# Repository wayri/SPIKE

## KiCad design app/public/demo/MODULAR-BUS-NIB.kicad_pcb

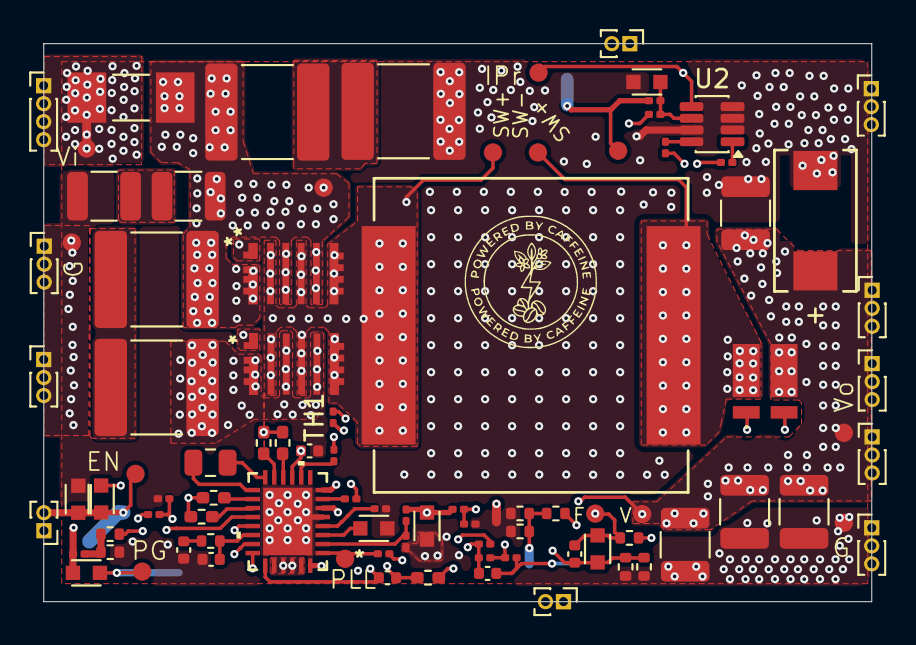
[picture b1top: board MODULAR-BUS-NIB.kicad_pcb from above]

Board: 6 copper layers, 46.0 x 31.0 mm, 91 parts (0 on the bottom side), 45 nets.

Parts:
C1, C2, C3, C4: 15u_100V_2220; C_2220_5750Metric
C9, C10: 4.7u_100V_1210; C_1210_3225Metric
C11: 33u_35V_2917; CAPMP7.6X4.3_3.1N_KEM-L
C13, C14, C15, C16: 22u_25V_1210; C_1210_3225Metric
C17: 100n_100V_0805; C_0805_2012Metric
C18: 4.7u_16V_0603; C_0603
C19, C24: 1n_50V_0402; C_0402_1005Metric
C20: 47p_50V_0402; C_0402_1005Metric
C21: 100n_16V_0201; C_0201_0603Metric
C22: 430p_50V_0402; C_0402_1005Metric
C23: 200p_50V_0402; C_0402_1005Metric
C25: 100n_25V_0603; C_0603
C26: 100n_10V_0201; C_0201_0603Metric
F1: 10A_125V; FUSC6125X279N
J1: Conn_01x04_Pin; PinHeader_1x04_P1.00mm_Vertical
J9, J12, J21: Conn_01x02_Pin; PinHeader_1x02_P1.00mm_Vertical
J14, J15, J16, J17, J18, J19, J20: Conn_01x03_Pin; PinHeader_1x03_P1.00mm_Vertical
JP1, JP2: Jumper_2_Open; R_0201_0603Metric
L2: 8.2u_18A; IND_SRP1770TA_BRN-M
NT1: NetTie_2; NetTie-2_SMD_Pad0.5mm
Q1, Q2: EPC2306; EPC2302ENGRT_ECC
R3, R4: 2R_0.33W_0402; R_0402_1005Metric_Pad0.72x0.64mm_HandSolder
R5, R6: 4R_0.33W_0402; R_0402_1005Metric_Pad0.72x0.64mm_HandSolder
R7, R30: 0R_0.1W_0603; C_0603
R8: 100R_0.063W_0402; R_0402_1005Metric_Pad0.72x0.64mm_HandSolder
R9, R13, R16, R17, R18, R21, R22, R26, R27, R28, R29, R32: 0R_0.05W_0201; C_0201_0603Metric
R10: 5R1_0.07W_0402; R_0402_1005Metric
R11: 140K_0.1W_0603; R_0603
R12, R20, R35, R36, R37: 20K_0.1W_0402; R_0402_1005Metric
R14: 124K_0.21W_0603; R_0603
R15, R24: 15K_0.1W_0402; R_0402_1005Metric
R19: 0R002_3W_1216; WSK12162L000FEA
R23: 110K_0.1W_0603; R_0603
R25: 4.7K_0.1W_0402; R_0402_1005Metric
R33: 20K_0.05W_0201; C_0201_0603Metric
R34: 24K_0.07W_0201; C_0201_0603Metric
R39: 100K_0.05W_0402; C_0402_1005Metric
TH1: 100K_0201; R_0201_0603Metric
TP2, TP3, TP4, TP5, TP6, TP7, TP8, TP9, TP10, TP11, TP12, TP13, TP14, TP15: TestPoint; TestPoint-1.0mm
U1: LTC7891RUFDM-PBF; 05-08-1682_ADI
U2: INA241A3QDDFRQ1; SOT-23-8

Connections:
/12Vout: C11.1, C13.1, C14.1, C15.1, C16.1, J14.1, J14.2, J14.3, J15.1, J15.2, J15.3, J20.1, J20.2, J20.3, R9.1, R10.2, R19.3, R21.1, R24.1, R36.1, TP3.1 (1_1), TP8.1 (1_1)
/BuckModuleIP22-60-OP12-P120W-DR/BGDN: R6.1, U1.13 (BGDN)
/BuckModuleIP22-60-OP12-P120W-DR/BGUP: R5.1, U1.12 (BGUP)
/BuckModuleIP22-60-OP12-P120W-DR/EN: J21.2, R7.1, R30.2, TP12.1 (1_1), U1.28 (RUN)
/BuckModuleIP22-60-OP12-P120W-DR/GHS: Q1.1, R3.2, R4.2
/BuckModuleIP22-60-OP12-P120W-DR/GLS: Q2.1, R5.2, R6.2
/BuckModuleIP22-60-OP12-P120W-DR/INTVCC: C18.1, C24.2, R13.1, R28.2, R32.1, U1.8 (DRVCC), U1.11 (INTVCC), U1.24 (DTCB), U1.25 (DTCA), U1.26 (DRVSET), U1.27 (DRVUV)
/BuckModuleIP22-60-OP12-P120W-DR/ISNS+: JP1.1 (A), R8.2, R19.1
/BuckModuleIP22-60-OP12-P120W-DR/ISNS-: C19.1, JP2.1 (A), R19.2, U1.23 (SENSE-)
/BuckModuleIP22-60-OP12-P120W-DR/ITH: C23.1, R15.1, U1.20 (ITH)
/BuckModuleIP22-60-OP12-P120W-DR/PLL: R18.1, TP2.1 (1_1), U1.1 (PLLIN/SPREAD)
/BuckModuleIP22-60-OP12-P120W-DR/SW_node: L2.2, Q1.3, Q1.5, Q1.7, Q2.3, Q2.5, Q2.7, TP4.1 (1_1)
/BuckModuleIP22-60-OP12-P120W-DR/TGDN: R4.1, U1.16 (TGDN)
/BuckModuleIP22-60-OP12-P120W-DR/TGUP: R3.1, U1.17 (TGUP)
/BuckModuleIP22-60-OP12-P120W-DR/VFB: C20.2, R11.2, R12.1, R20.1, U1.21 (VFB)
/BuckModuleIP22-60-OP12-P120W-DR/VPRG: R28.1, R29.1, U1.6 (VPRG)
/BuckModuleIP22-60-OP12-P120W-DR/Vext_3V3: J12.2, R22.2, R23.1, R26.2, R33.2, TP13.1 (1_1)
/BuckModuleIP22-60-OP12-P120W-DR/Vin: C1.1, C3.1, C9.1, F1.2, Q1.2, Q1.4, Q1.6, R7.2, R17.1, R18.2, TP6.1 (1_1)
/IPRPM: J12.1, TP14.1 (1_1), U2.5
/PG: J21.1, R23.2, TP11.1 (1_1), U1.18 (PGOOD)
/Tsns: C26.1, J9.1, R39.1
/Vin_f: F1.1, J1.1, J1.2, J1.3, J1.4, TP9.1 (1_1)
/Vsns: J9.2, R35.1, R36.2, R37.1
GND: C2.2, C4.2, C10.2, C11.2, C13.2, C14.2, C15.2, C16.2, C18.2, C21.1, C22.2, C23.2, C24.1, C25.2, J16.1, J16.2, J16.3, J17.1, J17.2, J17.3, J18.1, J18.2, J18.3, J19.1, J19.2, J19.3, NT1.1, Q2.2, Q2.4, Q2.6, R12.2, R14.2, R16.1, R20.2, R25.2, R27.1, R29.2, R30.1, R35.2, R37.2, TP10.1 (1_1), TP15.1 (1_1), U1.5 (TEST), U1.29 (GND), U2.2 (GND), U2.3 (REF2), U2.4 (GND), U2.7 (REF1)
unnamed: C1.2, C2.1
unnamed: C3.2, C4.1
unnamed: C9.2, C10.1
unnamed: C20.1, R10.1, R11.1, TP7.1 (1_1)
unnamed: C22.1, R15.2
unnamed: C26.2, NT1.2, R34.1, TH1.2
unnamed: JP1.2 (B), U2.8 (+)
unnamed: JP2.2 (B), U2.1 (-)
unnamed: L2.1, R19.4, TP5.1 (1_1)
unnamed: R24.2, R25.1, R26.1
unnamed: R33.1, R34.2, R39.2, TH1.1
unnamed: C17.1, U1.14 (BOOST)
unnamed: R9.2, U1.10 (EXTVCC)
unnamed: R14.1, U1.3 (FREQ)
unnamed: R16.2, R32.2, U1.19 (ILIM)
unnamed: R13.2, R27.2, U1.2 (MODE)
unnamed: C19.2, R8.1, U1.22 (SENSE+)
unnamed: C17.2, U1.15 (SW)
unnamed: C21.2, U1.4 (TRACK/SS)
unnamed: R17.2, U1.7 (VIN)
unnamed: C25.1, R21.2, R22.1, U2.6 (V+)

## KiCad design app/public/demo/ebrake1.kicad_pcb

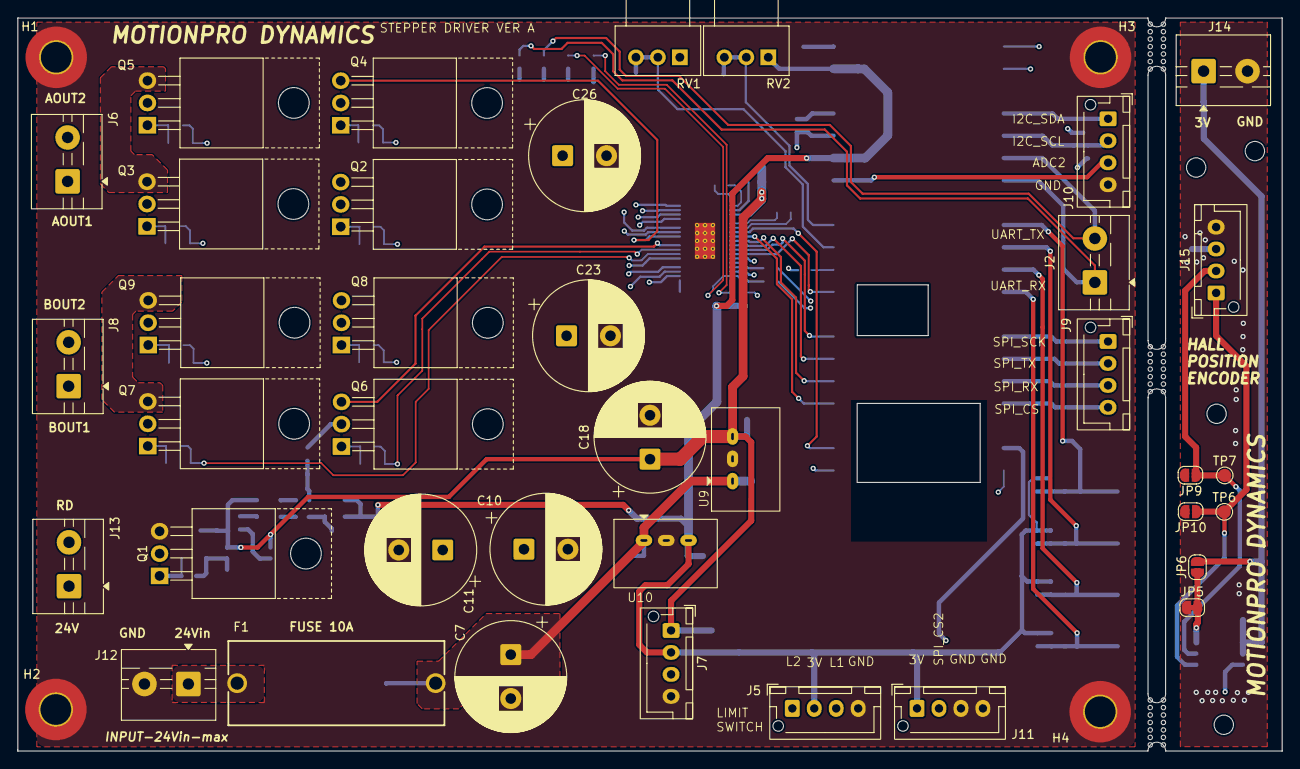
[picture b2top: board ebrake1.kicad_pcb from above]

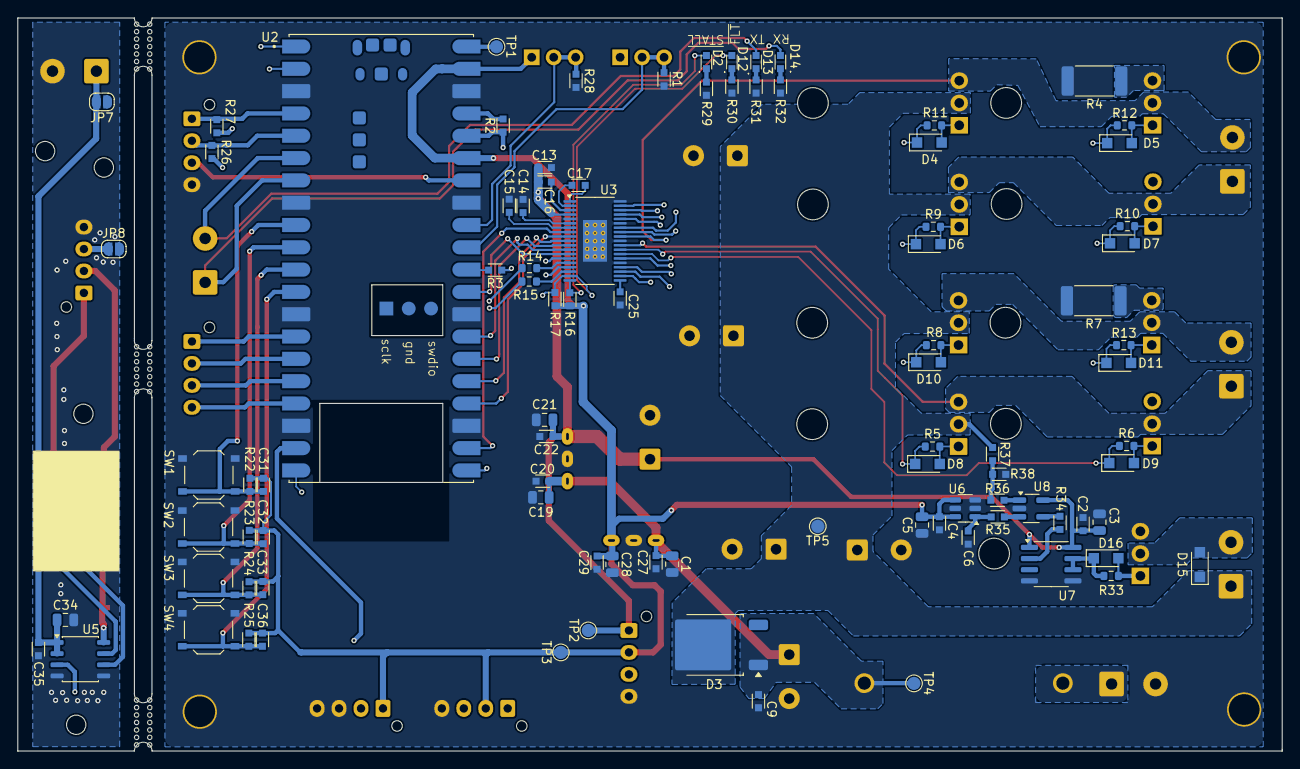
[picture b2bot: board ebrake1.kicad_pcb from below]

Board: 4 copper layers, 143.9 x 83.5 mm, 134 parts (92 on the bottom side), 84 nets.

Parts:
C1, C3, C5, C19, C21, C28, C34: 10u_50V; C_0805_2012Metric
C2, C4, C6, C9, C13, C15, C17, C20, C22, C27, C29, C31, C32, C33, C35, C36: 100n_50V; C_0603
C7, C10, C11, C18, C23, C26: 100u_100V; CP_Radial_D12.5mm_P5.00mm
C14, C16: 1u_50V; C_0603
C25: 1n_50V; C_0603
D2, D12: red; LED_0603
D3: 15A_100V; TO-252-2
D4, D5, D6, D7, D8, D9, D10, D11, D15, D16: SMD310HL-TP; Nexperia_CFP3_SOD-123W
D13, D14: yellow; LED_0603
F1: Fuse_holder_10A; 696108003002
H1, H2, H3, H4: MountingHole_Pad; MountingHole_3.5mm_Pad_TopOnly
J2, J6, J8, J12, J13, J14: stb01x02; TerminalBlock_MaiXu_MX126-5.0-02P_1x02_P5.00mm
J5, J7, J9, J10, J11, J15: 01x04; JST_XH_B4B-XH-AM_1x04_P2.50mm_Vertical
JP5: SolderJumper_2_Bridged; SolderJumper-2_P1.3mm_Bridged_RoundedPad1.0x1.5mm
JP6, JP7, JP8, JP9, JP10: SolderJumper_2_Open; SolderJumper-2_P1.3mm_Open_RoundedPad1.0x1.5mm
Q1, Q2, Q3, Q4, Q5, Q6, Q7, Q8, Q9: STP60NF06L; TO-220-3_Horizontal_TabUp
R1, R2, R3, R16, R17, R22, R23, R24, R25, R26, R27, R28, R29, R30, R31, R32, R34, R35, R36: 1k_0603; R_0603
R4, R7: 0.033R_2512; R_2512_6332Metric_Pad1.40x3.35mm_HandSolder
R5, R6, R8, R9, R10, R11, R12, R13, R14, R15, R33: 10R_0603; R_0603_1608Metric
R37: 10k_0603; R_0603
R38: 1.02k_0603; R_0603
RV1, RV2: R_Potentiometer_Trim; Potentiometer_Alps_RK09Y11_Single_Horizontal
SW1, SW2, SW3, SW4: SW_MEC_5E; SW_Push_1P1T_XKB_TS-1187A
TP1, TP2, TP3, TP4, TP5, TP6, TP7: TestPoint; TestPoint_Pad_D1.5mm
U2: SC0918; MODULE_SC0918
U3: DRV8711; HTSSOP-38-1EP_4.4x9.7mm_P0.5mm_EP2.74x4.75mm_ThermalVias
U5: AS5600L-ASOM; JEITA_SOIC-8_3.9x4.9mm_P1.27mm
U6: MCP1501-25xCH; SOT-23-6
U7: TC4420VOA713; SOIC-8_3.9x4.9mm_P1.27mm
U8: TLV1701AIDBVR; SOT-23-5_HandSoldering
U9: RBT10W24S12; rtb10_fp
U10: RBT10W24S3V3; rtb10_fp

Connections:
3Vin: C4.1, C5.1, C28.1, C29.1, C31.2, C32.2, C33.2, C36.2, J5.2, J7.2, J11.1, R16.2, R17.2, R22.1, R23.1, R24.1, R25.1, RV1.1, RV2.1, TP3.1, U2.35 (ADC_VREF), U2.39 (VSYS), U6.4 (~SHDN), U6.6 (VDD), U10.3 (Vout)
3Vout: R2.1, R3.1, R26.1, R27.1, U2.36 (3V3_OUT)
12V: C2.1, C3.1, C13.1, C16.1, C18.1, C21.1, C22.1, J7.1, TP2.1, U3.4 (VM), U7.1 (VDD), U7.8 (VDD), U8.5 (V+), U9.3 (Vout)
24V: C10.1, C11.1, C23.1, C26.1, D3.2 (K), D15.1 (K), J13.1, Q2.2 (D), Q4.2 (D), Q6.2 (D), Q8.2 (D), R37.2, TP5.1
24Vaux: C1.1, C7.1, C9.1, C19.1, C20.1, C27.1, D3.1 (A), F1.2, TP4.1, U9.1 (Vin), U10.1 (Vin)
/ADC0: R1.1, RV1.2, RV1.3, U2.31 (GP26)
/ADC1: R28.1, RV2.2, RV2.3, U2.32 (GP27)
/ADC2: J10.3, U2.34 (GP28)
/AOUT1: J6.1, Q2.3 (S), Q3.2 (D), U3.37 (AOUT1)
/AOUT2: J6.2, Q4.3 (S), Q5.2 (D), U3.30 (AOUT2)
/BIN1: U2.27 (GP21), U3.12 (BIN1)
/BIN2: U2.29 (GP22), U3.13 (BIN2)
/BOUT1: J8.1, Q6.3 (S), Q7.2 (D), U3.28 (BOUT1)
/BOUT2: J8.2, Q8.3 (S), Q9.2 (D), U3.21 (BOUT2)
/DIR: U2.26 (GP20), U3.11 (DIR/AIN2)
/ENC_OUT_ANLG: J15.3, JP8.1 (A), U5.3 (OUT)
/HBridge1/A1HS: D8.1 (K), R5.1, U3.27 (B1HS)
/HBridge1/A1LS: D9.1 (K), R6.1, U3.26 (B1LS)
/HBridge1/A2HS: D10.1 (K), R8.2, U3.22 (B2HS)
/HBridge1/A2LS: D11.1 (K), R13.2, U3.23 (B2LS)
/HBridge1/AISENP: Q7.3 (S), Q9.3 (S), R7.1, U3.25 (BISENP)
/HBridge/A1HS: D6.1 (K), R9.1, U3.36 (A1HS)
/HBridge/A1LS: D7.1 (K), R10.1, U3.35 (A1LS)
/HBridge/A2HS: D4.1 (K), R11.2, U3.31 (A2HS)
/HBridge/A2LS: D5.1 (K), R12.2, U3.32 (A2LS)
/HBridge/AISENP: Q3.3 (S), Q5.3 (S), R4.1, U3.34 (AISENP)
/I2C0_SCL: J10.2, R26.2, U2.5 (GP3)
/I2C0_SDA: J10.1, R27.2, U2.4 (GP2)
/LIM_SW1: J5.1, U2.1 (GP0)
/LIM_SW2: J5.3, U2.2 (GP1)
/RESET: U2.24 (GP18), U3.9 (RESET)
/SPI1_CS: J9.4, U2.17 (GP13), U3.16 (SCS)
/SPI1_CS2: J11.2, U2.19 (GP14)
/SPI1_RX: J9.3, R15.1, U2.16 (GP12)
/SPI1_SCK: J9.1, U2.14 (GP10), U3.14 (SCLK)
/SPI1_TX: J9.2, R14.1, U2.15 (GP11)
/STEP: U2.25 (GP19), U3.10 (STEP/AIN1)
/SW1: C31.1, R22.2, SW1.2, U2.9 (GP6)
/SW2: C32.1, R23.2, SW2.2, U2.10 (GP7)
/SW3: C33.1, R24.2, SW3.2, U2.11 (GP8)
/SW4: C36.1, R25.2, SW4.2, U2.12 (GP9)
/UART1_RX: D14.2 (A), J2.1, U2.7 (GP5)
/UART1_TX: D13.2 (A), J2.2, U2.6 (GP4)
/VCC_3V3: C34.1, C35.1, J14.1, JP6.2 (B), JP7.2 (B), U5.1 (VDD5V), U5.2 (VDD3V3)
/~FLT: D12.2 (A), R17.1, U2.20 (GP15), U3.18 (FAULTn)
/~SLEEP: U2.22 (GP17), U3.8 (SLEEPn)
/~STALL: D2.2 (A), R16.1, U2.21 (GP16), U3.19 (STALLn/BEMFVn)
GND: C1.2, C2.2, C3.2, C4.2, C5.2, C6.2, C7.2, C9.2, C10.2, C11.2, C13.2, C14.2, C15.2, C18.2, C19.2, C20.2, C21.2, C22.2, C23.2, C25.2, C26.2, C27.2, C28.2, C29.2, C34.2, C35.2, H1.1, H2.1, H3.1, H4.1, J5.4, J7.4, J10.4, J11.3, J11.4, J12.2, J14.2, J15.4, JP5.1 (A), Q1.3 (S), R1.2, R4.2, R7.2, R28.2, R29.2, R30.2, R31.2, R32.2, R38.1, SW1.1, SW2.1, SW3.1, SW4.1, U2.3 (GND), U2.8 (GND__1), U2.13 (GND__2), U2.18 (GND__3), U2.23 (GND__4), U2.28 (GND__5), U2.33 (AGND), U2.38 (GND__6), U2.F (GND__7), U3.5 (GND), U3.24 (BISENN), U3.29 (GND), U3.33 (AISENN), U3.38 (GND), U3.39 (GND), U5.4 (GND), U5.5 (PGO), U6.2 (GND), U6.3 (GND), U6.5 (GND), U7.4 (GND), U7.5 (GND), U8.2 (V-), U9.2 (GND), U10.2 (GND)
unnamed: D2.1 (K), R29.1
unnamed: D4.2 (A), Q4.1 (G), R11.1
unnamed: D5.2 (A), Q5.1 (G), R12.1
unnamed: D6.2 (A), Q2.1 (G), R9.2
unnamed: D7.2 (A), Q3.1 (G), R10.2
unnamed: D8.2 (A), Q6.1 (G), R5.2
unnamed: D9.2 (A), Q7.1 (G), R6.2
unnamed: D10.2 (A), Q8.1 (G), R8.1
unnamed: D11.2 (A), Q9.1 (G), R13.1
unnamed: D12.1 (K), R30.1
unnamed: D13.1 (K), R31.1
unnamed: D14.1 (K), R32.1
unnamed: D15.2 (A), J13.2, Q1.2 (D)
unnamed: D16.2 (A), Q1.1 (G), R33.2
unnamed: D16.1 (K), R33.1, U7.6 (OUT), U7.7 (OUT)
unnamed: F1.1, J12.1
unnamed: J15.1, JP10.1 (A), TP6.1, U5.6 (SDA)
unnamed: J15.2, JP9.1 (A), TP7.1, U5.7 (SCL)
unnamed: JP5.2 (B), JP6.1 (A), U5.8 (DIR)
unnamed: R36.1, R37.1, R38.2
unnamed: R2.2, U2.37 (3V3_EN)
unnamed: TP1.1, U2.40 (VBUS)
unnamed: R3.2, U2.30 (~RUN)
unnamed: C25.1, U3.20 (BEMF)
unnamed: C17.2, U3.1 (CP1)
unnamed: C17.1, U3.2 (CP2)
unnamed: R14.2, U3.15 (SDATI)
unnamed: R15.2, U3.17 (SDATO)
unnamed: C14.1, U3.6 (V5)
unnamed: C16.2, U3.3 (VCP)
unnamed: C15.1, U3.7 (VINT)
unnamed: C6.1, R35.1, U6.1 (OUT)
unnamed: R34.2, U7.2 (INPUT)
unnamed: R36.2, U8.1 (IN+)
unnamed: R35.2, U8.3 (IN-)
unnamed: R34.1, U8.4 (OUT)

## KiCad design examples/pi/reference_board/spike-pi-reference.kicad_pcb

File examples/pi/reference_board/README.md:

<!-- SPDX-License-Identifier: MIT -->

# SPIKE PI reference board and examples

This is an original synthetic KiCad board generated for SPIKE's PI examples.
Copyright (c) 2026 Yawar Badri; the board, generator, example runner, and this
directory's documentation are available under [MIT](LICENSE). No third-party
board file, footprint geometry, screenshot, 3D model, or private project data
is included. This board has not been fabricated or measured.

The board has four nets: `VIN`, `VLOAD`, `VAUX`, and `GND`. `VIN` crosses an
explicit 0.1 ohm R1 series interface to `VLOAD`. The latter contains top and
bottom traces, two plated vias, and one filled zone. `VAUX` is a straight trace
for an independent resistance oracle. C2 is the nominal placed VLOAD capacitor
site; C3 is an unpopulated comparison site. Nominal board copper is 35 um per
side, and the 1.53 mm core uses relative permittivity 4.2 and loss tangent
0.02. These are fixture assumptions, not a fabrication stackup.

Run from a checkout with SPIKE's Python dependencies and native PEEC extension:

```sh
python examples/pi/reference_board/generate_board.py
python examples/pi/reference_board/run.py --output build/pi-reference-evidence.json --html-dir build/pi-reference-html
python examples/pi/reference_board/run_kernel_benchmarks.py --output build/pi-kernel-benchmarks.json
```

The deterministic board UUIDs and SHA-256 in the evidence detect accidental
fixture changes. The runner exercises KiCad import, validation, preflight and
hybrid mesh, DC on three rails, quasi-static AC on three rails, three-level DC
mesh convergence, reviewed R1 series-path AC, board-derived PDN multiport,
placed-C2 versus DNP-C3 capacitor sensitivity, an independent 17-frequency
nodal loading reference, multi-net batch normalization, and JSON/HTML reports.
The runner exits nonzero when any of its executable checks fails.
The separate kernel runner selects exactly ten retained PI references from
the internal benchmark implementations. It fails if any case fails or skips;
its checked [output](validation/pi-kernel-benchmarks.json) records every
measured value, oracle, error, and tolerance. These checks cover straight
trace and plated-via resistance, zone refinement, hybrid connectivity, native
self-inductance, hybrid PEEC, a capacitance limit, AC loss monotonicity,
shared-reference multiport algebra, and independent capacitor loading.

The closed-form VAUX DC oracle is `R = L/(sigma*w*t)` with `L=35 mm`,
`w=0.8 mm`, `t=35 um`, and `sigma=5.8e7 S/m`. The 2% tolerance allows pad
attachment geometry; it is not a global PI solver accuracy claim. DC power
balance is checked within 1%. AC checks require completed, passive sampled
impedance and finite residuals. C2/C3 use the same provisional 47 uF,
8 mOhm ESR, 0.6 nH ESL model and a 50 mOhm target for a *sensitivity study*.
No load profile, regulator, capacitor derating, mounting parasitics, return
impedance, or measured data justifies an operating-board optimum.

The evidence deliberately reports `release_validated: false`. Completing this
synthetic example does not qualify Marble, CERN, or other real-board behavior.
The stage-one release also requires a separate source/package parity gate,
real-board convergence and passivity evidence, clean-machine builds, and
knowledgeable numerical review. Preserve failures rather than changing a
tolerance to turn a blocked result into a pass.

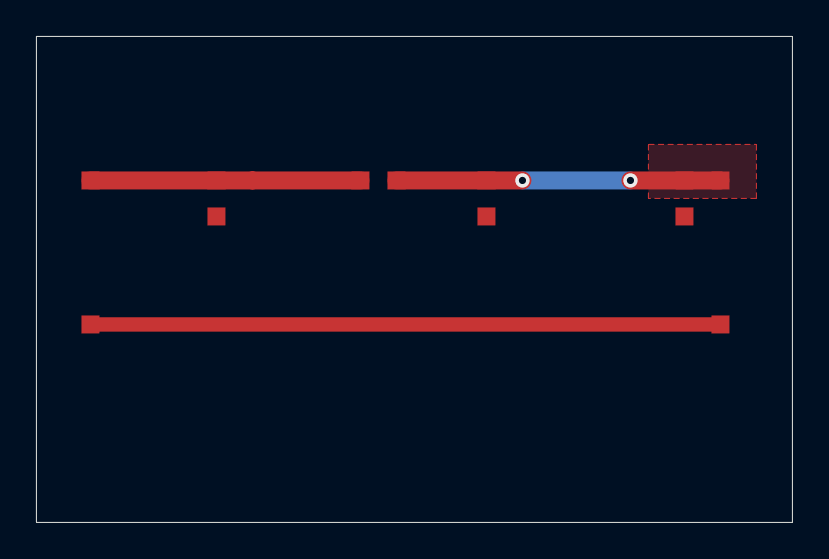
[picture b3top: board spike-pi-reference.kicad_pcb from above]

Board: 2 copper layers, 42.0 x 27.0 mm, 8 parts (0 on the bottom side), 4 nets.

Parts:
C1: 47u placed VIN decoupler; PI_Test
C2: 47u placed VLOAD decoupler; PI_Test
C3: DNP VLOAD comparison site; PI_Test
J1: VIN source; PI_Test
J2: VLOAD load; PI_Test
J3: VAUX source; PI_Test
J4: VAUX load; PI_Test
R1: series interface; PI_Test

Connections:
GND: C1.2, C2.2, C3.2
VAUX: J3.1, J4.1
VIN: C1.1, J1.1, R1.1
VLOAD: C2.1, C3.1, J2.1, R1.2
